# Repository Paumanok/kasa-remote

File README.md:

# Kasa-remote

An ESP32 based remote control device for manipulating and monitoring TPLink Kasa devices.

Future plans include new control modules, power saving, and other nice-to-haves. 

Leverages [rust_kasa](https://github.com/Paumanok/rust_kasa)

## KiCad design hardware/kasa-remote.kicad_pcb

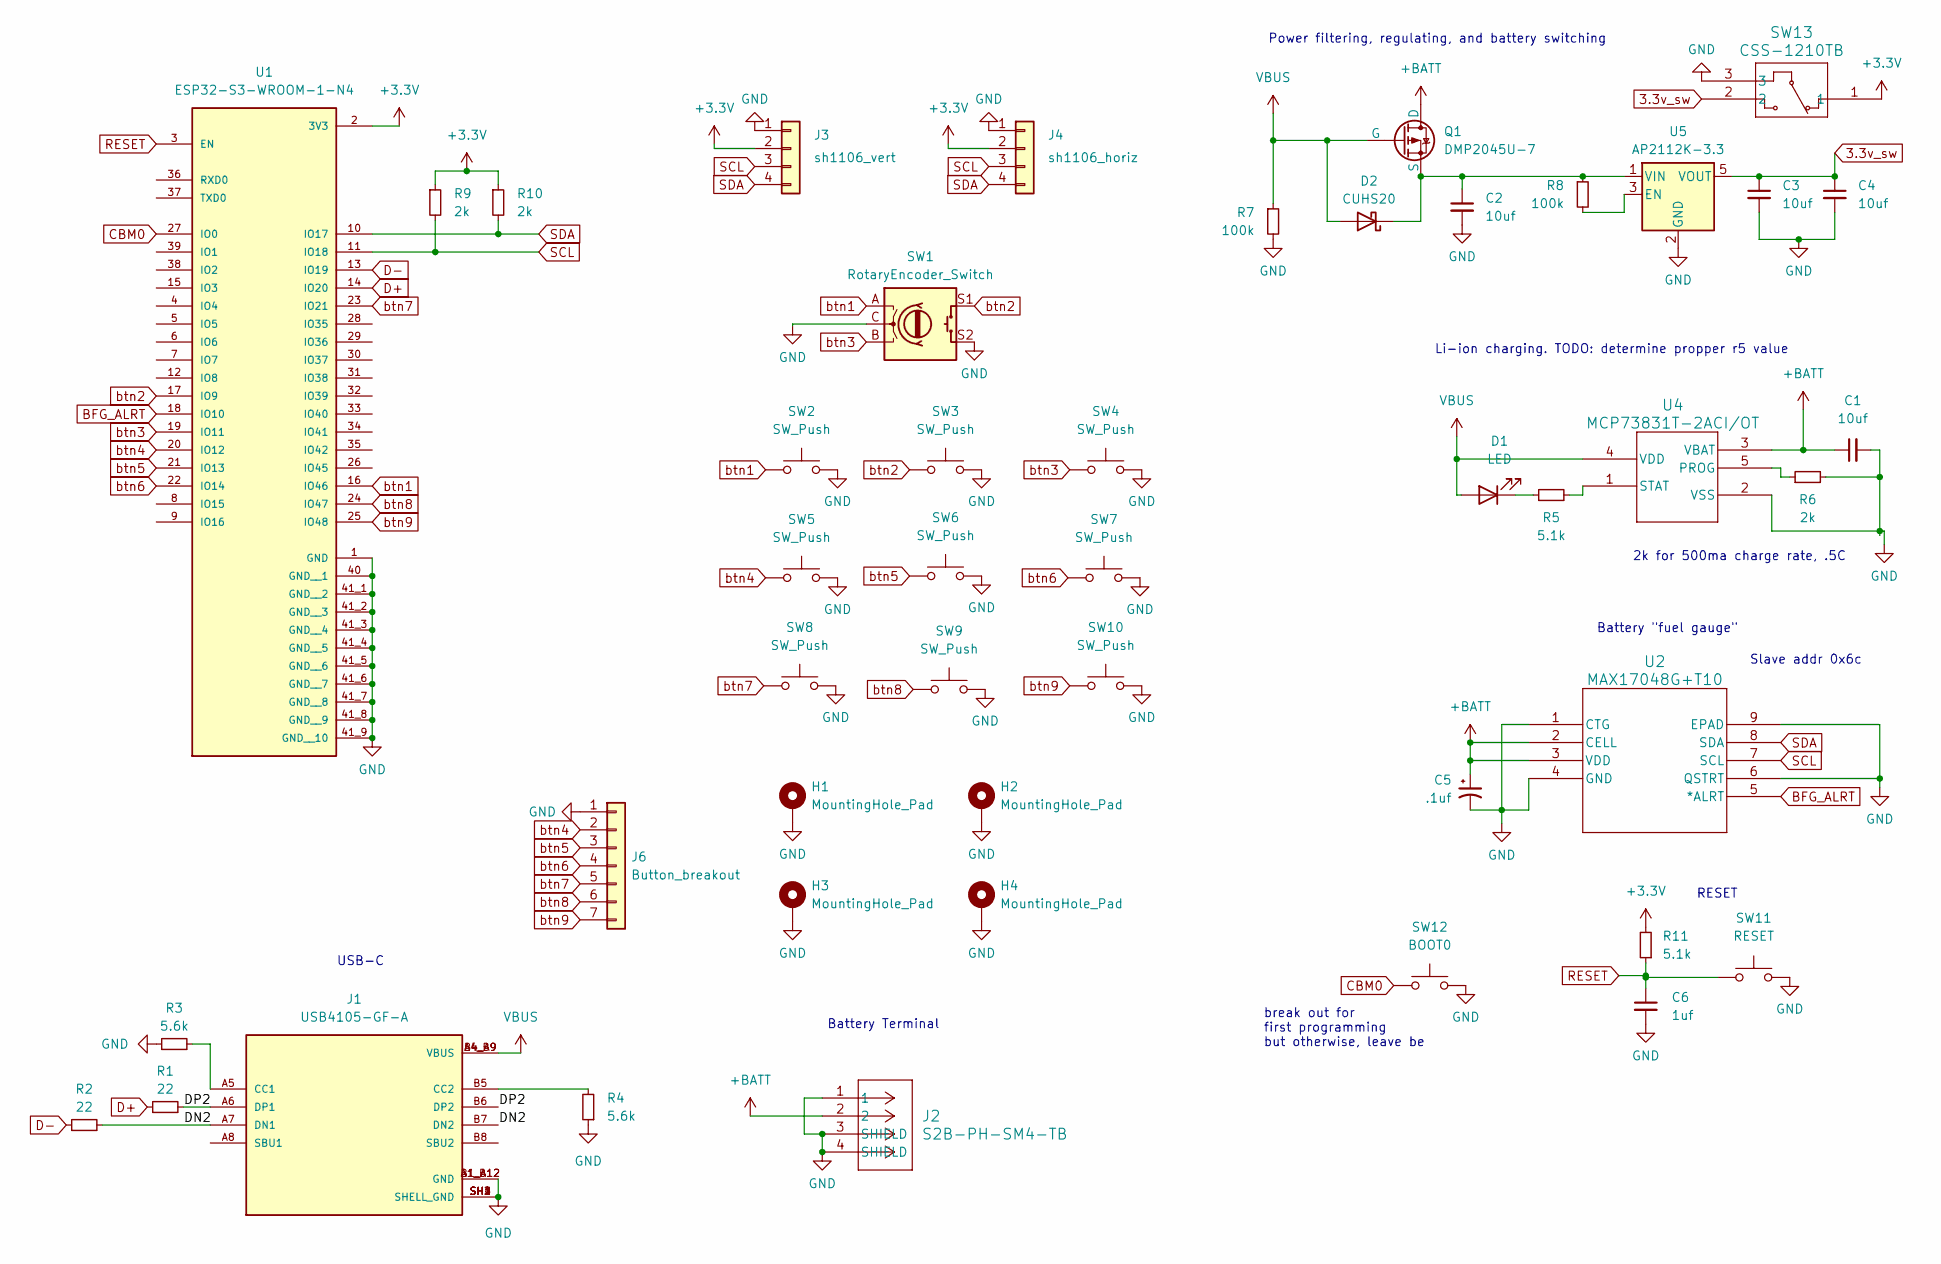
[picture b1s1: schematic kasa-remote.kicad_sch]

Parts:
C1, C2, C3, C4: 10uf; C_0603_1608Metric
C5: .1uf; C_0603_1608Metric
C6: 1uf; C_0603_1608Metric
D1: LED; LED_0603_1608Metric
D2: CUHS20; US2H_TOS
H1, H2, H3, H4: MountingHole_Pad; MountingHole_2.2mm_M2_DIN965_Pad_TopBottom
J1: USB4105-GF-A; GCT_USB4105-GF-A; PARTREV B3
J2: S2B-PH-SM4-TB; CONN_S2B-PH-SM4-TB_JST
J3: sh1106_vert; PinHeader_1x04_P2.54mm_Vertical
J4: sh1106_horiz; PinHeader_1x04_P2.54mm_Vertical
J6: Button_breakout; PinHeader_1x07_P2.54mm_Vertical
Q1: DMP2045U-7; SOT-23_DIO; Mfg Part # DMP2045U-7
R1, R2: 22; R_0603_1608Metric; mpn CR0603-FX-22R0ELF
R3, R4: 5.6k; R_0603_1608Metric
R5, R11: 5.1k; R_0603_1608Metric
R6, R9, R10: 2k; R_0603_1608Metric
R7, R8: 100k; R_0603_1608Metric
SW1: RotaryEncoder_Switch; RotaryEncoder_Alps_EC11E-Switch_Vertical_H20mm
SW2, SW3, SW4, SW5, SW6, SW7, SW8, SW9, SW10: SW_Push; SW_SPST_PTS645; mpn CKN10880CT-ND
SW11: RESET; SW_SPST_PTS810; mpn PTS815 SJM 250 SMTR LFS
SW12: BOOT0; SolderJumper-2_P1.3mm_Open_RoundedPad1.0x1.5mm
SW13: CSS-1210TB; CSS-1210TB_NDC
U1: ESP32-S3-WROOM-1-N4; ESP32-S3-WROOM-1; PARTREV v1.0
U2: MAX17048G+T10; 21-0168E_T822-3_MXM
U4: MCP73831T-2ACI/OT; SOT-23-5_MC_MCH
U5: AP2112K-3.3; SOT-23-5

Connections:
3.3v_sw: C3.1, C4.1, SW13.2, U5.5 (VOUT)
+3.3V: J3.2, J4.2, R9.1, R10.1, R11.2, SW13.1, U1.2 (3V3)
+BATT: C1.1, C5.1, J2.2, Q1.1 (D), U2.2 (CELL), U2.3 (VDD), U4.3 (VBAT)
/DN2: J1.A7 (DN1), J1.B7 (DN2), R2.2
/DP2: J1.A6 (DP1), J1.B6 (DP2), R1.2
BFG_ALRT: U1.18 (IO10), U2.5 (*ALRT)
CBM0: SW12.1, U1.27 (IO0)
D+: R1.1, U1.14 (IO20)
D-: R2.1, U1.13 (IO19)
GND: C1.2, C2.2, C3.2, C4.2, C5.2, C6.2, H1.1, H2.1, H3.1, H4.1, J1.A1_B12 (GND), J1.B1_A12 (GND), J1.SH1 (SHELL_GND), J1.SH2 (SHELL_GND), J1.SH3 (SHELL_GND), J1.SH4 (SHELL_GND), J2.1, J2.3 (SHIELD), J2.4 (SHIELD), J3.1, J4.1, J6.1, R3.1, R4.1, R6.2, R7.2, SW1.C, SW1.S2, SW2.2, SW3.2, SW4.2, SW5.2, SW6.2, SW7.2, SW8.2, SW9.2, SW10.2, SW11.2, SW12.2, SW13.3, U1.1 (GND), U1.40 (GND__1), U1.41_1 (GND__2), U1.41_2 (GND__3), U1.41_3 (GND__4), U1.41_4 (GND__5), U1.41_5 (GND__6), U1.41_6 (GND__7), U1.41_7 (GND__8), U1.41_8 (GND__9), U1.41_9 (GND__10), U2.1 (CTG), U2.4 (GND), U2.6 (QSTRT), U2.9 (EPAD), U4.2 (VSS), U5.2 (GND)
unnamed: D1.1 (K), R5.1
unnamed: C2.1, D2.1 (K), Q1.3 (S), R8.1, U5.1 (VIN)
unnamed: J1.A5 (CC1), R3.2
unnamed: J1.B5 (CC2), R4.2
unnamed: R6.1, U4.5 (PROG)
unnamed: R5.2, U4.1 (STAT)
unnamed: R8.2, U5.3 (EN)
RESET: C6.1, R11.1, SW11.1, U1.3 (EN)
SCL: J3.3, J4.3, R9.2, U1.11 (IO18), U2.7 (SCL)
SDA: J3.4, J4.4, R10.2, U1.10 (IO17), U2.8 (SDA)
VBUS: D1.2 (A), D2.2 (A), J1.A4_B9 (VBUS), J1.B4_A9 (VBUS), Q1.2 (G), R7.1, U4.4 (VDD)
btn1: SW1.A, SW2.1, U1.16 (IO46)
btn2: SW1.S1, SW3.1, U1.17 (IO9)
btn3: SW1.B, SW4.1, U1.19 (IO11)
btn4: J6.2, SW5.1, U1.20 (IO12)
btn5: J6.3, SW6.1, U1.21 (IO13)
btn6: J6.4, SW7.1, U1.22 (IO14)
btn7: J6.5, SW8.1, U1.23 (IO21)
btn8: J6.6, SW9.1, U1.24 (IO47)
btn9: J6.7, SW10.1, U1.25 (IO48)

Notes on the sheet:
Power filtering, regulating, and battery switching
RESET
Slave addr 0x6c
Battery "fuel gauge"
Li-ion charging. TODO: determine propper r5 value
break out for first programming but otherwise, leave be
2k for 500ma charge rate, .5C
USB-C
Battery Terminal

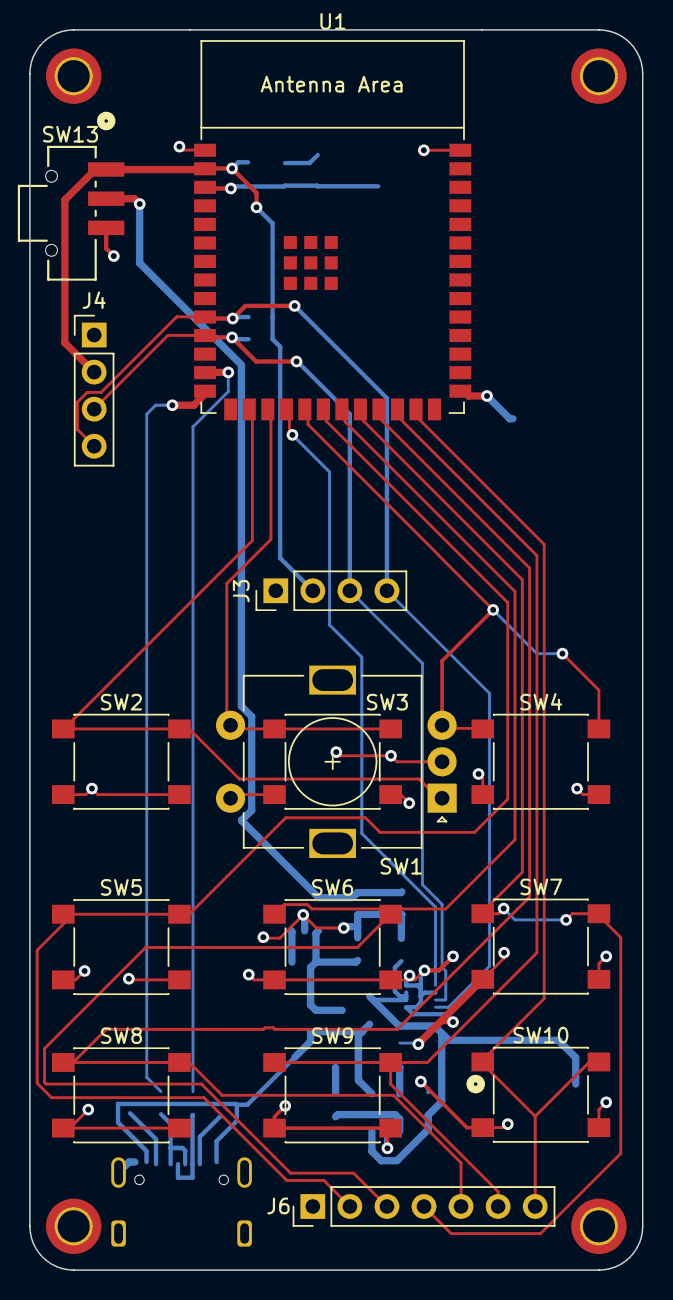
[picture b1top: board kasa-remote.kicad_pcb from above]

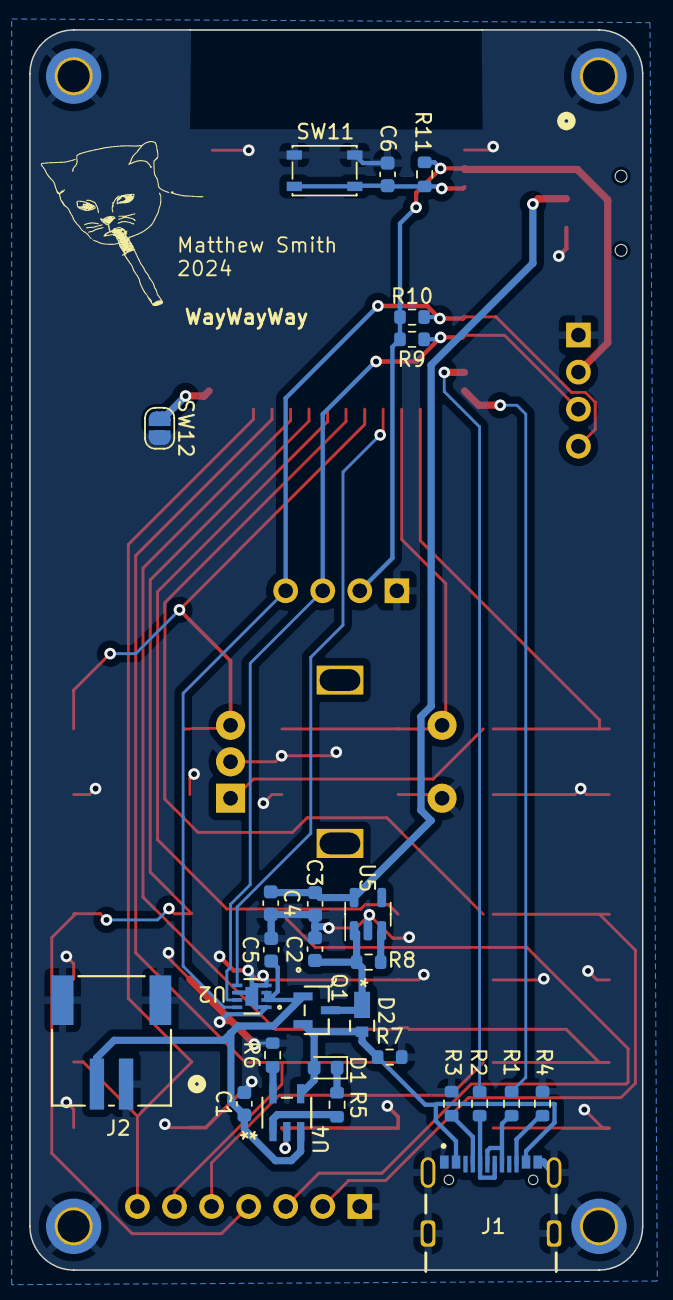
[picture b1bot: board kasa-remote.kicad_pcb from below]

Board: 2 copper layers, 42.0 x 85.0 mm, 46 parts (27 on the bottom side), 30 nets.

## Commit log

2024-02-10 making it more complex, laying ground work for some threads
2024-02-11 code is quite messy but I've got some threaded tasks going for updating the display and getting live data
2024-02-12 made some stability improvements with more error checking. Added some wifi reconnect logic.
2024-02-12 house keeping
2024-02-14 drafting the UI and trying to get the encoder going. currently broken
2024-02-14 found a nice blog post, encoder working nice
2024-02-16 changed encoder implementation, not currently wired up to send current val to display service. Going to re-do how everything is interconnected. Still a little slow for my liking so I may need to sepa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
2024-02-17 switched from channels to a Arc<Mutex<>> and set up an api polling thread and things are a lot snappier. Happy with the responsiveness of the encoder for now
2024-02-17 some reorganization of the peripheral driving code so I don't need to scroll up and down as much
2024-02-17 cleaned up the encoder service, removing the need to specify the pin in the function signature
2024-02-18 complicating the display service so I can be lazy
2024-03-04 putting the kicad stuff into git
2024-03-05 starting pcb work, might need to add more to the gitignore
2024-03-06 fixed a couple mistakes in the schematic, organizing and starting layout
2024-03-10 layout just about done, no more errors at least
2024-03-10 still tweaking silkscreens
2024-03-10 cleaned up the silkscreen errors
2024-03-10 added some graphics
2024-03-10 just about done, I think I want to move the horizontal display over a bit so it's symetrical to the pcb
2024-03-12 added the waywayway for pcb way, also added the bom spreadsheet
2024-03-19 doing bringup on the new pcb
2024-03-20 all the buttons brought up and functioning. I need to figure out a real debounce strategy
2024-03-21 Removed dependency on std-training wifi library, began breaking out peripheral services/structs/enums into submodules
2024-03-23 added proper button debouncing and broke out button actions from service
2024-03-27 began the work on the module runner service which will be able to take a vec of trait objects and dispatch them as needed. also ran cargo fmt so there's a bunch of changes
2024-03-27 no longer can do remote things right now but the module dispatcher is functional
2024-04-02 still not working, but started moving kasa stuff to new runner framework in order to work out practical necessities
2024-04-02 forgot to add the kasa_control
2024-04-02 trying the dual mpsc route, hoping the delay isn't too bad, almost done wiring it up
2024-04-02 proof of concept module thread switching with display and IO channels
2024-04-02 reintroduced wifi to the mix, i have my light switch back. Also ran cargo fmt so a lot of small changes there
2024-04-04 worked out some better flow control that makes display updates snappier
2024-04-06 small timing changes, picture in the readme
2024-04-07 starting integration for the battery monitor, turns out the singleton i2c bus is going to cause some issues
2024-04-08 not working but its getting closer
2024-04-08 thank you dirbaio on the rust embedded matrix for showing me box::leak
2024-04-09 good news: max170xx working, bad news: whole new bottle of worms to put that i2c handle into the BatteryMonitor struct. it will be a tomorrow problem. otherwise, we have a shared i2c device bus acros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
2024-04-10 sensor working, need some display improvements
2024-04-10 added a stopgap solution for selectively clearing the display so I can have both battery% and current module displaying at once
2024-04-13 moved wifi init, added some state to the battery reading
2024-04-13 something broke wifi, investigating
2024-04-13 readding clear_rect, still unsure what is causing the issue
2024-04-13 working on desktop, weird
2024-04-14 removed a lot of unneeded code, ran cargo fmt, commented out the whole rotary file awaiting its own refactoring
2024-04-14 minor tweaks, reducing task stack sizes for simpler tasks
2024-04-16 Cleaning up some comments, added a display_error function, to provide a quick interface for throwing a visual error on the display. Moved the wifi module into peripheral util. Cleaned up cargo.toml. 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
2024-07-06 changes to support new rust_kasa signatures
2024-08-18 reworking display a little bit to accept an arbitrary buffer as a render option
2024-08-19 made da box move
2024-08-19 some timing tuning
2024-08-30 workin on snake
2024-08-31 got a little dot to move, not quite a snake yet
2024-08-31 score goes away now
2024-09-01 broke test module into its own file, moved module definition out of the moduleRunner constructor, made the snek move like a snek
2024-09-01 snake game functionally done, woo
2024-09-01 fixed some comments
2024-12-07 starting to add support for multiple devices to control
2024-12-07 ran fmt, added logic for single outlets
